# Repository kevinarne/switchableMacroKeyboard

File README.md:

# Switchable Macro Keyboard
Many programs, such as Inkscape, have some pretty intricate keyboard shortcuts that I find challenging to use regularly, so I've made a macro keyboard that can be switched between different macro keyboards.

At the moment, the code only supports sending static strings, like "Hooray" or "Wow, that's crazy," but eventually it will also support modifier keys like shift and control.

# Components
* Arduino Pro Micro
* 12 x Cherry MX buttons
* 12 x diodes
* 3D printed housing
* 3D printed knob
* LCD Panel
* 7 x 10k ohm resistors
* 1 x rotary encoder
* Micro USB cable
* Custom PCB (see gerber.zip)

# Next Steps
* Encapsulate keyboard logic in an object
* Add long-press detection to keyboard and rotary encoder
* Add screen animations
* Create scripting language for complicated key sequences
* Remove old LCD code

# Programming
To program using the Arduino environment, make sure to set your board to Arduino Leonardo. There are several test sketches in the src/test folder that you can use to test individual components in isolation, but the main sketch is in the src/macroKeyMain folder along with the keyboards.h file that contains the different macro keyboards to be loaded.

If you simply want this to work as a macro keyboard, but with your own commands, you should only have to change the keyboards.h file and upload the code to your Arduino Pro Micro.

Note: the main sketch has no checks on any of the data in keyboards.h. Although the code may compile and upload, **failure to correctly format keyboards.h can result in index out of bounds errors, causing the keyboard to stop working until power cycled.**

You will need to have the following libraries installed:
* Wire.h
* LiquidCrystal_I2C.h
* Keyboard.h

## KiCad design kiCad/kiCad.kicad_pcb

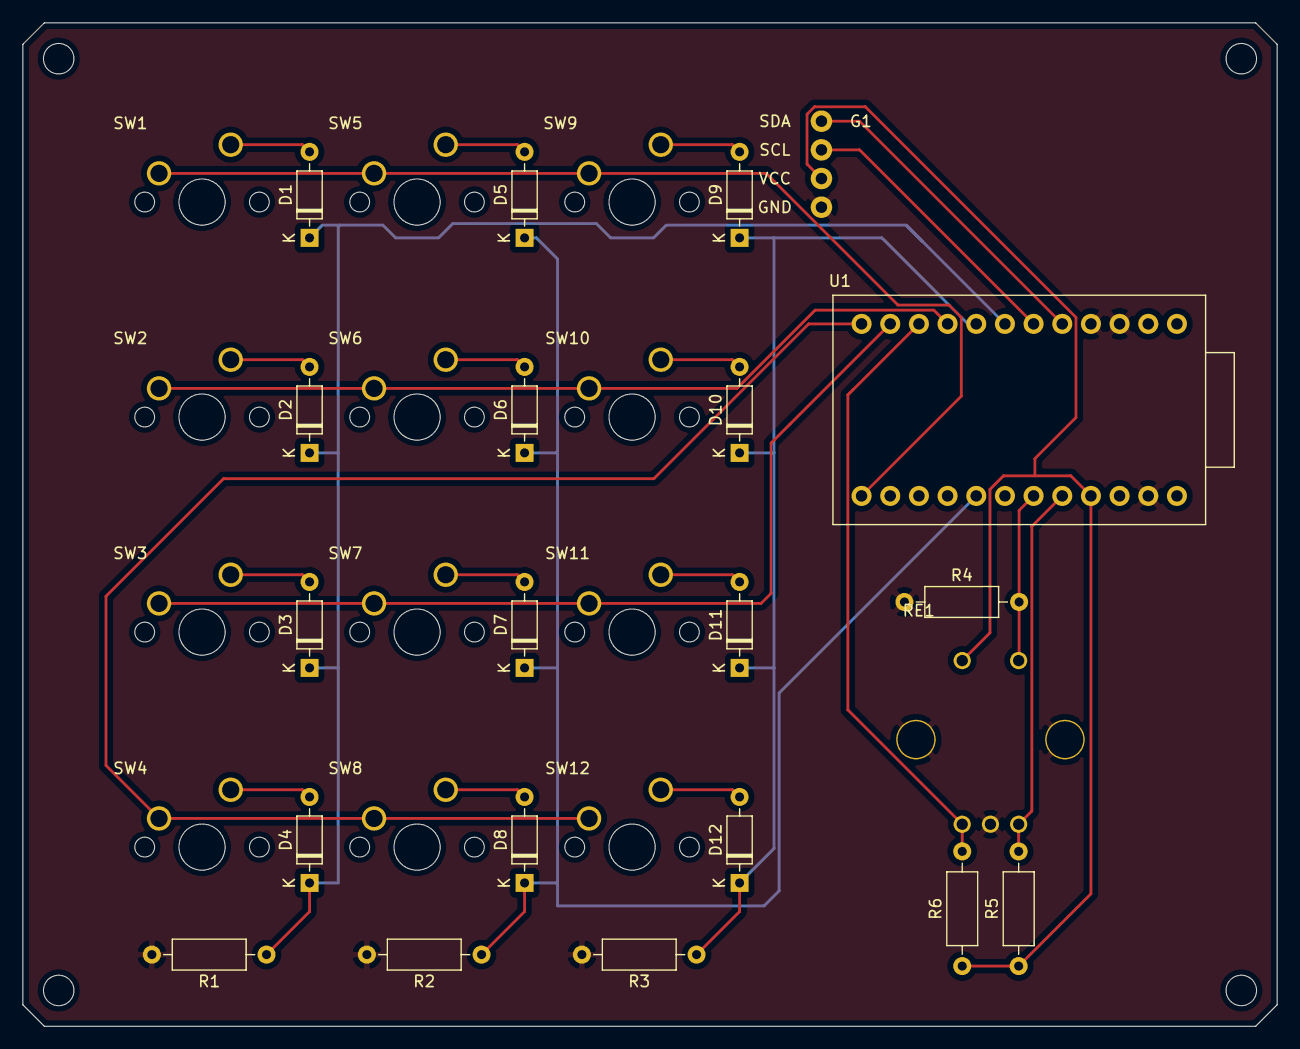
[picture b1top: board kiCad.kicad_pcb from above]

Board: 2 copper layers, 111.1 x 88.9 mm, 33 parts (0 on the bottom side), 26 nets.

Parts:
D1, D2, D3, D4, D5, D6, D7, D8, D9, D10, D11, D12: D; D_DO-35_SOD27_P7.62mm_Horizontal
G1: thinOLED
R1, R2, R3, R4, R5, R6: R_US; R_Axial_DIN0207_L6.3mm_D2.5mm_P10.16mm_Horizontal
RE1: RotaryEncoderWButton; REnc-PEC12R-Bourns
SW1, SW2, SW3, SW4, SW5, SW6, SW7, SW8, SW9, SW10, SW11, SW12: SW_Push; cherryMX
U1: ProMicro

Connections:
/COL0: D1.1, D2.1, D3.1, D4.1, R1.1, U1.7
/COL1: D5.1, D6.1, D7.1, D8.1, R2.1, U1.17
/COL2: D9.1, D10.1, D11.1, D12.1, R3.1, U1.8
/EN_CLK: R6.2, RE1.5, U1.10
/ROW0: SW1.1, SW5.1, SW9.1, U1.13
/ROW1: SW2.1, SW6.1, SW10.1, U1.9
/ROW2: SW3.1, SW7.1, SW11.1, U1.11
/ROW3: SW4.1, SW8.1, SW12.1, U1.12
/SCL: G1.2, U1.6
/SDA: G1.1, U1.5
GND: G1.4, R1.2, R2.2, R3.2, R4.1, RE1.4, RE1.6, RE1.7, U1.3, U1.4, U1.23
unnamed: D1.2, SW1.2
unnamed: D2.2, SW2.2
unnamed: D3.2, SW3.2
unnamed: D4.2, SW4.2
unnamed: D5.2, SW5.2
unnamed: D6.2, SW6.2
unnamed: D7.2, SW7.2
unnamed: D8.2, SW8.2
unnamed: D9.2, SW9.2
unnamed: D10.2, SW10.2
unnamed: D11.2, SW11.2
unnamed: D12.2, SW12.2
unnamed: R4.2, RE1.2, U1.19
unnamed: R5.2, RE1.3, U1.20
VCC: G1.3, R5.1, R6.1, RE1.1, U1.21

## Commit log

2020-04-21 Initial commit. Copied schematic from original design, added some more buttons (need wiring) and removed the header for the rotary encoder. To do: wire the new buttons, change buttons to tactile butt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
2020-04-21 Added blank Arduino files. To do: Add a switch to the input so it can be debugged appropriately.
2020-04-22 Added some pseudo code to source. Connected the switches to the Pro Micro
2020-04-22 Made rotary encoder footprint and symbol. Wired rotary encoder to Pro Micro. Added LCD breakout points. To do: replace switches with tactile switches, add an enable pin (2-pin jumper), and route.
2020-04-22 Changed to tact switches.
2020-04-22 Routed the entire board and added pulldown resistors to the columns. To do: sleep on it and order in the morning.
2020-04-22 Added an enable option to disable all output when broken for debugging purposes. Mitered all of the traces with a 40 mil miter. Changed the corners from filets to chamfers.
2020-04-22 Added gerber files for the boards I ordered.
2020-04-25 Added some more pseudo code and added loops to the keyboard function.
2020-04-25 Added pin numbers and some pseudocode.
2020-04-26 Addedmore structure to the keyboard scanning, including some digital reads. Added a toBeSent matrix that helps with communication between the keyboardScanning function and main loop. To do: setup the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
2020-04-27 Added SoftwareSerial initialization.
2020-04-27 Added Keyboard #include and begin().
2020-04-27 Added details on bringing the first board version up to speed. Added some position variables to macroKeyMain for the rotary encoder.
2020-04-29 Added enable pin debugging.
2020-04-29 Addedfunction for outputting the keyboard input matrix to the Serial output.
2020-05-01 Added test scripts for rotary encoder and enable pin. Rotary encoder test script still needs fleshing out. To do: write keyboard test script.
2020-05-01 Wrote keypad test and ran it on the device (passed). To do: add logic to send a key once to the keypad test.
2020-05-01 Added key sending. Successfully only sends the key at the first press when holding. No sign of bouncing.
2020-05-01 Folded the keyboard test scripts back into the macroKeyMain script. To do: work on rotary encoder script.
2020-05-02 Switched around visible layers on board for exporting a dxf. Added code loading info to README.md.
2020-05-02 Added lots of detail to encoder test. Got the position to change with a rotation in either direction (can't tell the difference between the two yet), but in serious need of debouncing.
2020-05-02 Added a good amount of pause for debouncing to REncTest.ino. Appears to work for most cases, but still gets the occasional double.
2020-05-02 Added source for rotary encoder info to the top of REncTest.ino.
2020-05-03 Made rotary encoder only trigger when the clock pin is 1. Reduced delay to 50, seems to have helped with the reliability at higher rotation speeds.
2020-05-03 Integrated the rotary encoder code in macroKeyMain.
2020-05-05 Added I2C header for LCD panel. Rearranged pinouts to open up I2C pins on the Pro Micro. To do: add labels to I2C bus and reroute board.
2020-05-06 Partially rerouted board with several pins moved around on the microcontroller for ease of routing. To do: route columns on bottom layer.
2020-05-25 Added a header file to hold all of the keyboards. Added an LCD test that works.
2020-05-25 Fixed all of the pinouts to reflect the new board layout. Adjusted the rotary encoder test to represent the new pins as well.
2020-05-25 Integrated keyboard, rotary encoder, and header file. To do: add LCD code to display keyboard name, create language for sending unusual key presses together.
2020-05-25 Implemented LCD panel to display keyboard name.
2020-05-25 Reformatted a lot of the code, adding spacing to comments and moving curly brackets around.
2020-05-27 Updated README.md. Moved LCD panel control to a dedicated function in case I change to a different display panel at some point. Updated gerber file to reflect the newest version of the boards.
2020-05-31 Integrated String parsing to allow for modifier keys. Finally hooked up the actual Keyboard library and found it all works. To do: make a new enclosure including the LCD panel, code for the keyboards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
2020-06-05 Added an Inkscape keyboard. Having trouble getting the stroke to path - break apart - union sequence to work right.
2020-06-05 Switched the buttons to Cherry MX Blues, but found this may require a bigger board, mostly length-wise. Moving the diodes out of the way of the key has cramped things. To do: adjust board dimensions 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
2020-06-10 Adjusted the size of the board and rerouted.
2020-07-06 Moved the Pro Micro board up to reduce interference with the key switches. Adjusted routing accordingly. Ordered this version in green.
2020-07-11 Changed footprints for Cherry MX keys to use holes rather than circles on the Dimension layer due to an issue at the board manufacturer.
2020-07-16 Updated Cherry foot print to fix holes too small for the pins.
2020-07-16 Adjusted routing to allow for the changed switch footprint.
2021-03-19 Started conversion from Eagle to KiCAD. Created rudimentary rotary encoder schematic symbol and footprint based on previous Eagle iteration. Created new schematic symbol for Pro Micro using a more fu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
2021-03-19 Added footprint for Pro Micro, next is the footprint for the keys.
2021-03-21 Finished schematic sans OLED screen, generated net list, placed components on board.
2021-03-22 Board routed but missing OLED screen, corner chamfers, mounting holes, logo, and switch footprint fix.
2021-03-22 Updated the switch footprints, chamfered corners, added mounting holes. Still need to add logo, but then it'll be ready for manufacturing.
2021-03-23 Added logo to solder mask layer (will show the underlying copper fill there). Sending out for manufacturing.
2021-03-23 Added KiCad-generated gerbers for this iteration of the macro keyboard PCB.
2021-03-23 Removed old Eagle files.
2021-06-11 Updated README.md, made a mess of everything else. Next step is to clean up and add a .gitignore file.
2021-06-11 Added .gitignore to clean things up a good bit.
